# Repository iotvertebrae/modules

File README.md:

# IoT Vertebrae 

The vertebrae bus is an extenxion of the [UEXT](https://www.olimex.com/Products/Modules/UEXT) open bus proposed by Olimex.

This project will be provided as open-source hardware.

## [Using IoT Vertebrae (Wiki)](https://www-binefa-com.translate.goog/index.php/IoT-Vertebrae?_x_tr_sl=ca&_x_tr_tl=en&_x_tr_hl=es&_x_tr_pto=wapp)

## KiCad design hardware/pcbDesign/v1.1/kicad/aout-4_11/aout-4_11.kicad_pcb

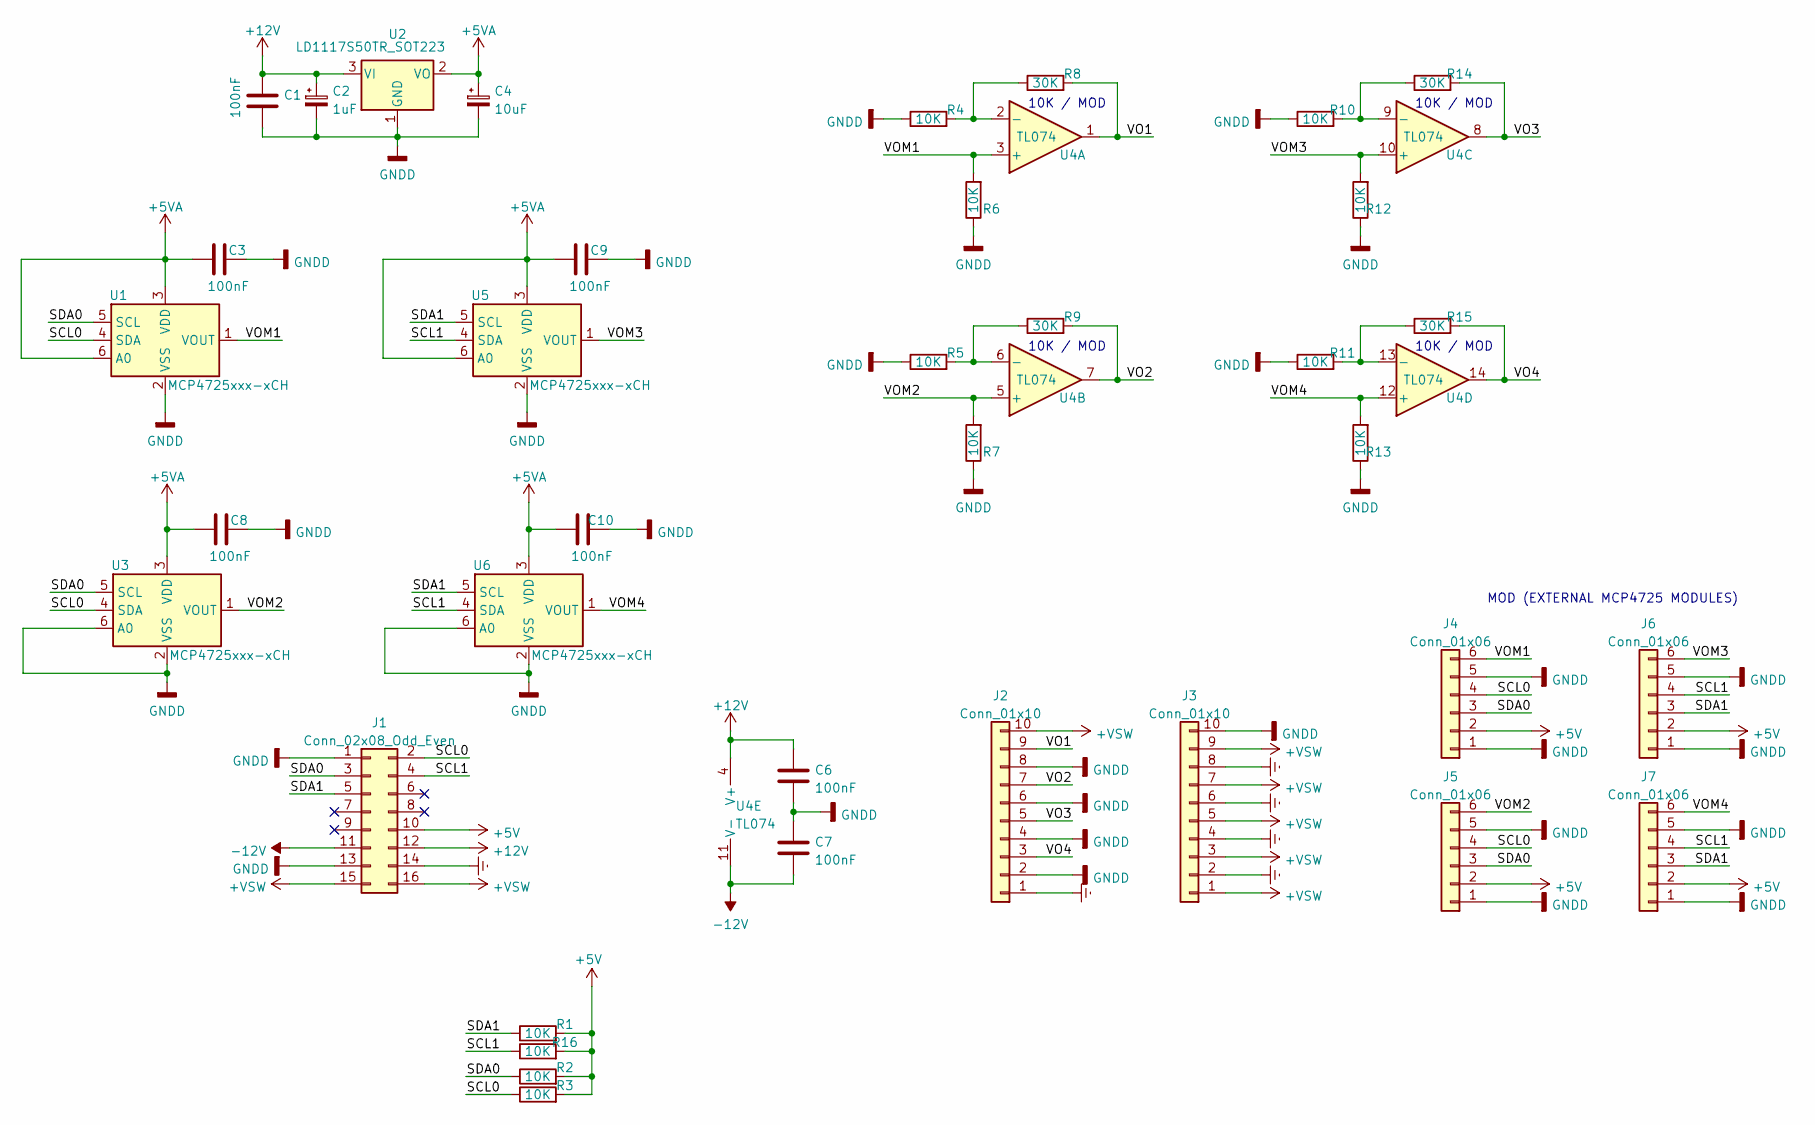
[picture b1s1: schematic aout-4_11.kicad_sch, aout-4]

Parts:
C1, C3, C6, C7, C8, C9, C10: 100nF; C_0805_2012Metric_Pad1.18x1.45mm_HandSolder
C2: 1uF; C_0805_2012Metric_Pad1.18x1.45mm_HandSolder
C4: 10uF; C_0805_2012Metric_Pad1.18x1.45mm_HandSolder
J1: Conn_02x08_Odd_Even; PinHeader_2x08_P2.54mm_Vertical
J2: Conn_01x10; PhoenixContact_MSTBA_2,5_10-G-5,08_1x10_P5.08mm_Horizontal
J3: Conn_01x10; PhoenixContact_MSTBVA_2,5_10-G-5,08_1x10_P5.08mm_Vertical
J4, J5, J6, J7: Conn_01x06; PinSocket_1x06_P2.54mm_Vertical
R1, R2, R3, R4, R5, R6, R7, R10, R11, R12, R13, R16: 10K; R_0805_2012Metric_Pad1.20x1.40mm_HandSolder
R8, R9, R14, R15: 30K; R_0805_2012Metric_Pad1.20x1.40mm_HandSolder
U1, U3, U5, U6: MCP4725xxx-xCH; SOT-23-6
U2: LD1117S50TR_SOT223; SOT-223-3_TabPin2
U4: TL074; SOIC-14_3.9x8.7mm_P1.27mm

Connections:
+5V: J1.10, J4.2, J5.2, J6.2, J7.2, R1.2, R2.2, R3.2, R16.2
+5VA: C3.1, C4.1, C8.1, C9.1, C10.1, U1.3 (VDD), U1.6 (A0), U2.2 (VO), U3.3 (VDD), U5.3 (VDD), U5.6 (A0), U6.3 (VDD)
+12V: C1.1, C2.1, C6.1, J1.12, U2.3 (VI), U4.4 (V+)
+VSW: J1.15, J1.16, J2.10, J3.1, J3.3, J3.5, J3.7, J3.9
-12V: C7.2, J1.11, U4.11 (V-)
/SCL0: J1.2, J4.4, J5.4, R3.1, U1.4 (SDA), U3.4 (SDA)
/SCL1: J1.4, J6.4, J7.4, R16.1, U5.4 (SDA), U6.4 (SDA)
/SDA0: J1.3, J4.3, J5.3, R2.1, U1.5 (SCL), U3.5 (SCL)
/SDA1: J1.5, J6.3, J7.3, R1.1, U5.5 (SCL), U6.5 (SCL)
/VO1: J2.9, R8.2, U4.1
/VO2: J2.7, R9.2, U4.7
/VO3: J2.5, R14.2, U4.8
/VO4: J2.3, R15.2, U4.14
/VOM1: J4.6, R6.2, U1.1 (VOUT), U4.3 (+)
/VOM2: J5.6, R7.2, U3.1 (VOUT), U4.5 (+)
/VOM3: J6.6, R12.2, U4.10 (+), U5.1 (VOUT)
/VOM4: J7.6, R13.2, U4.12 (+), U6.1 (VOUT)
Earth: J1.14, J2.1, J3.2, J3.4, J3.6, J3.8
GNDD: C1.2, C2.2, C3.2, C4.2, C6.2, C7.1, C8.2, C9.2, C10.2, J1.1, J1.13, J2.2, J2.4, J2.6, J2.8, J3.10, J4.1, J4.5, J5.1, J5.5, J6.1, J6.5, J7.1, J7.5, R4.1, R5.1, R6.1, R7.1, R10.1, R11.1, R12.1, R13.1, U1.2 (VSS), U2.1 (GND), U3.2 (VSS), U3.6 (A0), U5.2 (VSS), U6.2 (VSS), U6.6 (A0)
unnamed: R4.2, R8.1, U4.2 (-)
unnamed: R5.2, R9.1, U4.6 (-)
unnamed: R10.2, R14.1, U4.9 (-)
unnamed: R11.2, R15.1, U4.13 (-)

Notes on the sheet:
10K / MOD
MOD (EXTERNAL MCP4725 MODULES)

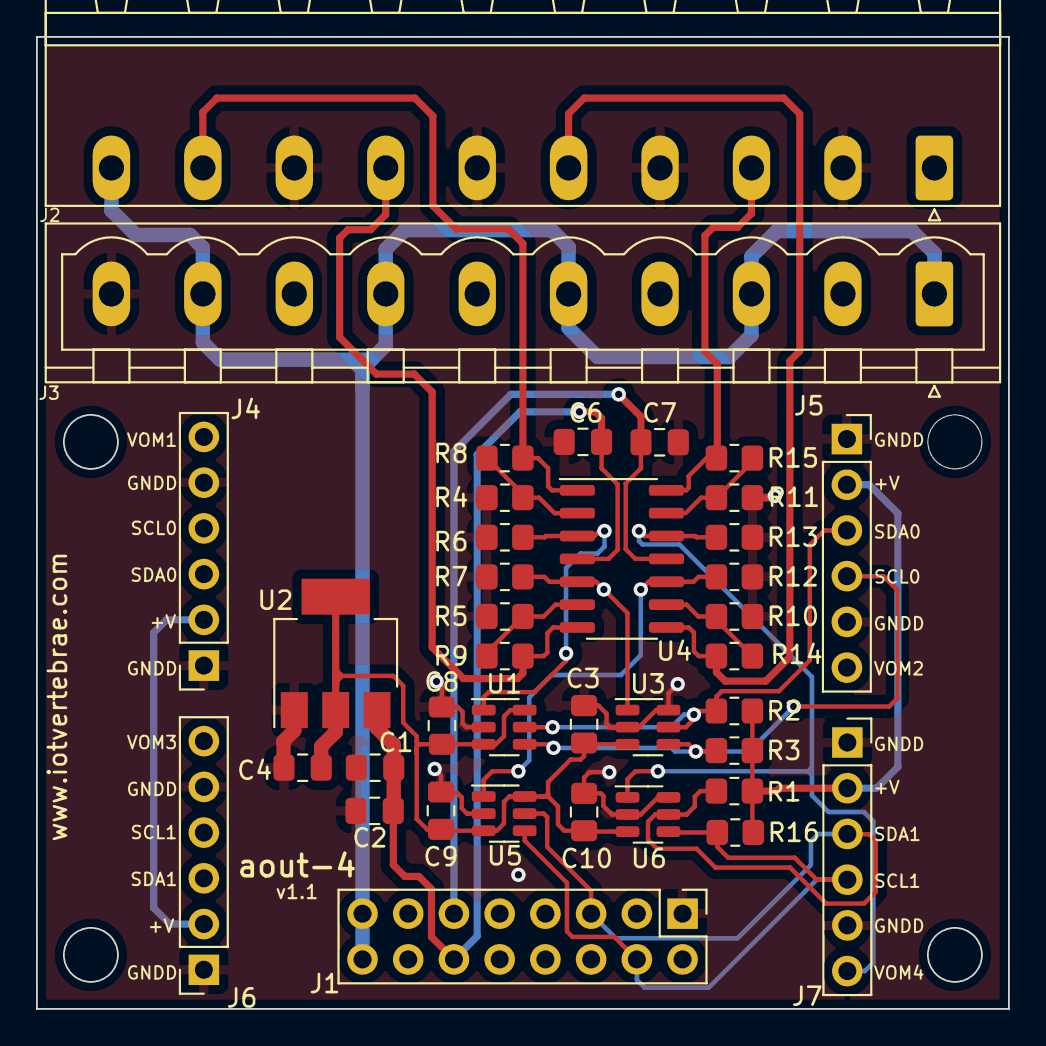
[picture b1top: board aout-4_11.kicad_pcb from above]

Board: 4 copper layers, 54.0 x 54.0 mm, 38 parts (0 on the bottom side), 23 nets.

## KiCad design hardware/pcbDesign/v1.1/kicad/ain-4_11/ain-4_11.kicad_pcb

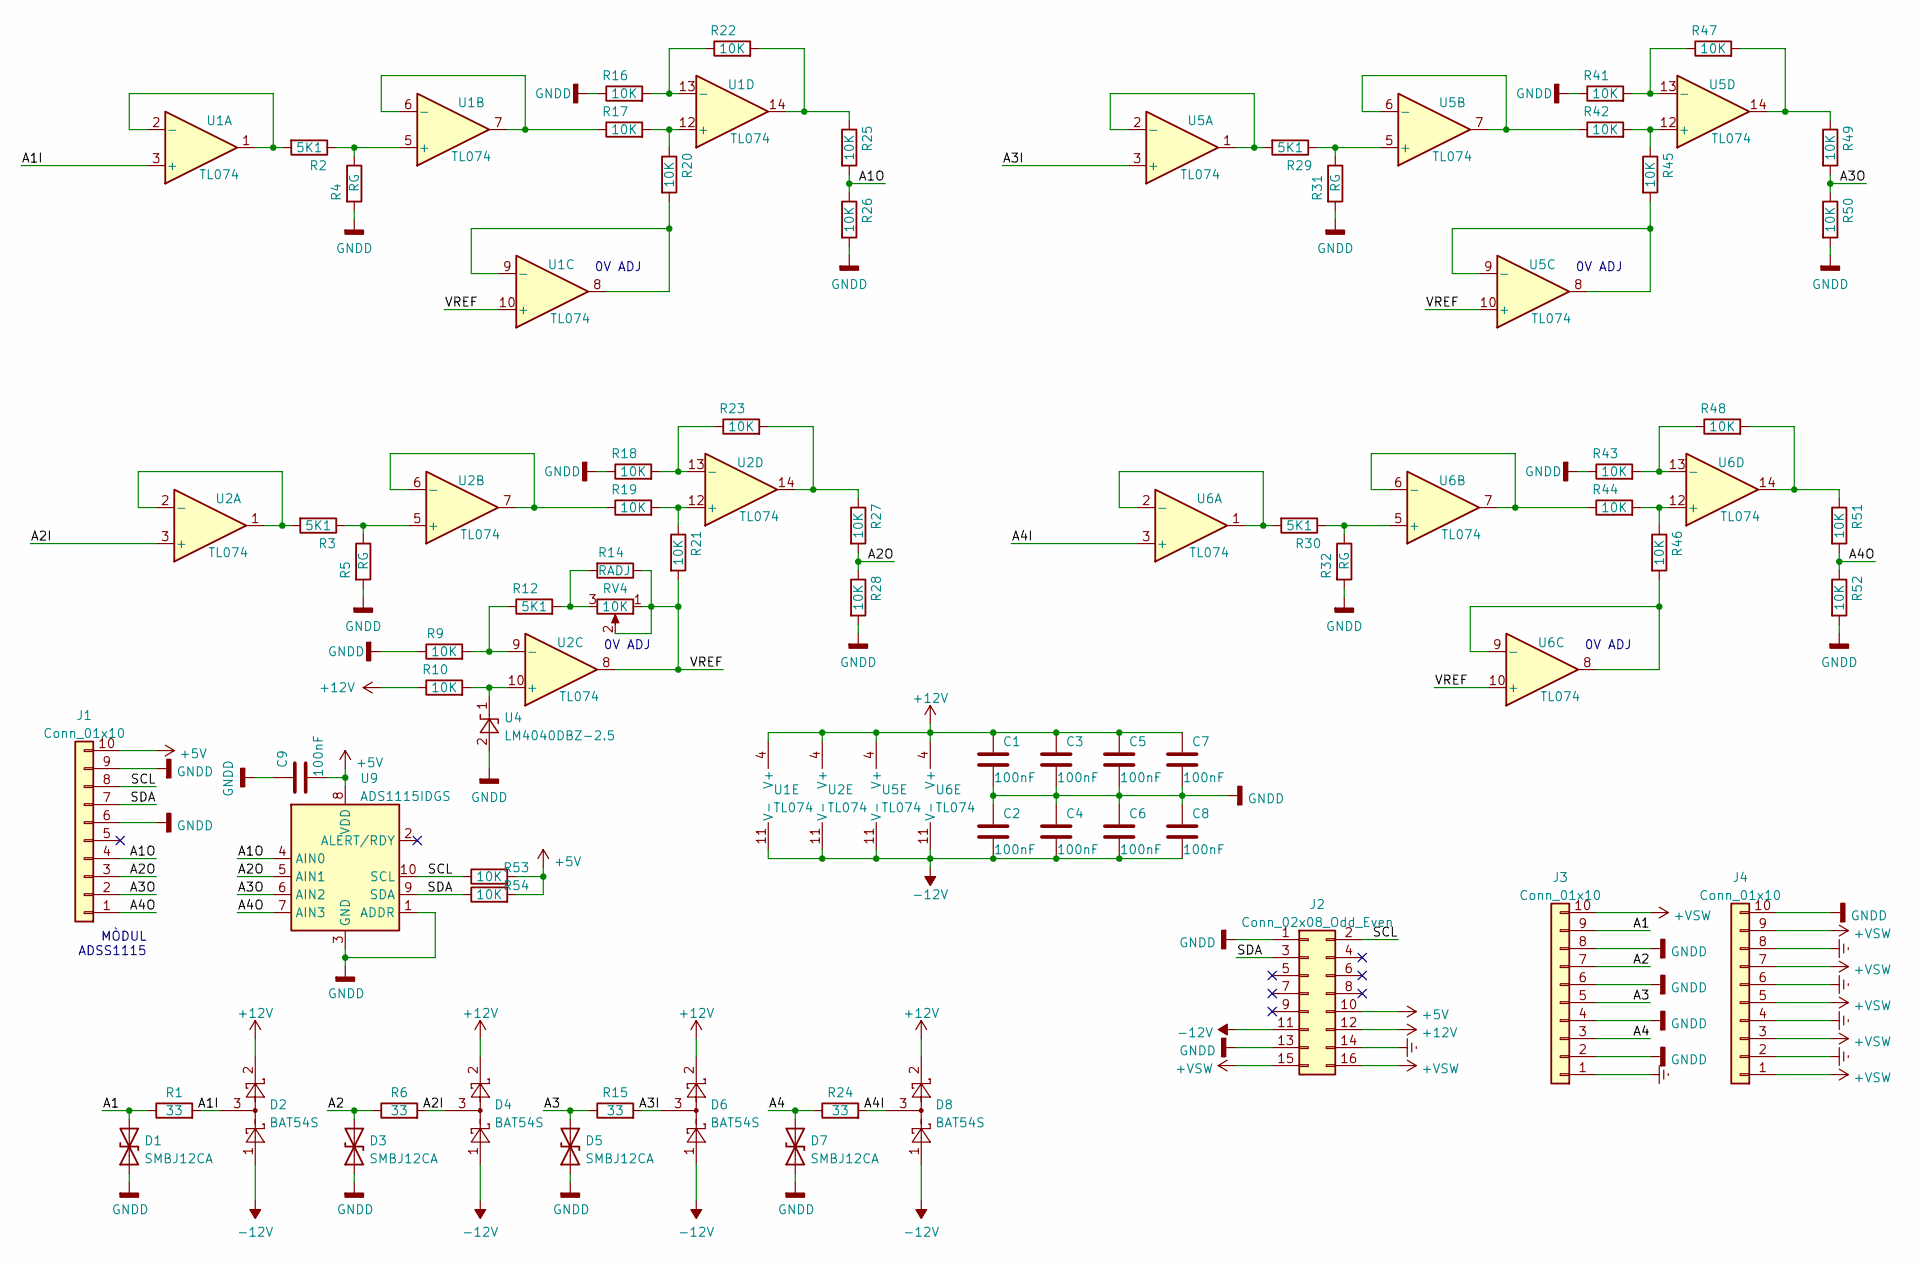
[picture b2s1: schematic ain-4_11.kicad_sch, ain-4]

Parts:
C1, C2, C3, C4, C5, C6, C7, C8, C9: 100nF; C_0805_2012Metric_Pad1.18x1.45mm_HandSolder
D1, D3, D5, D7: SMBJ12CA; D_SMB_Handsoldering
D2, D4, D6, D8: BAT54S; SOT-23
J1: Conn_01x10; PinSocket_1x10_P2.54mm_Vertical
J2: Conn_02x08_Odd_Even; PinHeader_2x08_P2.54mm_Vertical
J3: Conn_01x10; PhoenixContact_MSTBA_2,5_10-G_1x10_P5.00mm_Horizontal
J4: Conn_01x10; PhoenixContact_MSTBVA_2,5_10-G-5,08_1x10_P5.08mm_Vertical
R1, R6, R15, R24: 33; R_0805_2012Metric_Pad1.20x1.40mm_HandSolder
R2, R3, R12, R29, R30: 5K1; R_0805_2012Metric_Pad1.20x1.40mm_HandSolder
R4, R5, R31, R32: RG; R_0805_2012Metric_Pad1.20x1.40mm_HandSolder
R9, R10, R16, R17, R18, R19, R20, R21, R22, R23, R25, R26, R27, R28, R41, R42, R43, R44, R45, R46, R47, R48, R49, R50, R51, R52, R53, R54: 10K; R_0805_2012Metric_Pad1.20x1.40mm_HandSolder
R14: RADJ; R_0805_2012Metric_Pad1.20x1.40mm_HandSolder
RV4: 10K; Potentiometer_Bourns_3296W_Vertical
U1, U2, U5, U6: TL074; SOIC-14_3.9x8.7mm_P1.27mm
U4: LM4040DBZ-2.5; SOT-23
U9: ADS1115IDGS; TSSOP-10_3x3mm_P0.5mm

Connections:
+5V: C9.2, J1.10, J2.10, R53.2, R54.2, U9.8 (VDD)
+12V: C1.1, C3.1, C5.1, C7.1, D2.2, D4.2, D6.2, D8.2, J2.12, R10.1, U1.4 (V+), U2.4 (V+), U5.4 (V+), U6.4 (V+)
+VSW: J2.15, J2.16, J3.10, J4.1, J4.3, J4.5, J4.7, J4.9
-12V: C2.2, C4.2, C6.2, C8.2, D2.1, D4.1, D6.1, D8.1, J2.11, U1.11 (V-), U2.11 (V-), U5.11 (V-), U6.11 (V-)
/A1: D1.2 (A2), J3.9, R1.1
/A1I: D2.3, R1.2, U1.3 (+)
/A1O: J1.4, R25.2, R26.1, U9.4 (AIN0)
/A2: D3.2 (A2), J3.7, R6.1
/A2I: D4.3, R6.2, U2.3 (+)
/A2O: J1.3, R27.2, R28.1, U9.5 (AIN1)
/A3: D5.2 (A2), J3.5, R15.1
/A3I: D6.3, R15.2, U5.3 (+)
/A3O: J1.2, R49.2, R50.1, U9.6 (AIN2)
/A4: D7.2 (A2), J3.3, R24.1
/A4I: D8.3, R24.2, U6.3 (+)
/A4O: J1.1, R51.2, R52.1, U9.7 (AIN3)
/SCL: J1.8, J2.2, R53.1, U9.10 (SCL)
/SDA: J1.7, J2.3, R54.1, U9.9 (SDA)
/VREF: R14.1, R21.2, RV4.1, RV4.2, U1.10 (+), U2.8, U5.10 (+), U6.10 (+)
Earth: J2.14, J3.1, J4.2, J4.4, J4.6, J4.8
GNDD: C1.2, C2.1, C3.2, C4.1, C5.2, C6.1, C7.2, C8.1, C9.1, D1.1 (A1), D3.1 (A1), D5.1 (A1), D7.1 (A1), J1.6, J1.9, J2.1, J2.13, J3.2, J3.4, J3.6, J3.8, J4.10, R4.2, R5.2, R9.1, R16.1, R18.1, R26.2, R28.2, R31.2, R32.2, R41.1, R43.1, R50.2, R52.2, U4.2 (A), U9.1 (ADDR), U9.3 (GND)
unnamed: R2.1, R4.1, U1.5 (+)
unnamed: R2.2, U1.1, U1.2 (-)
unnamed: R3.1, R5.1, U2.5 (+)
unnamed: R3.2, U2.1, U2.2 (-)
unnamed: R10.2, U2.10 (+), U4.1 (K)
unnamed: R9.2, R12.1, U2.9 (-)
unnamed: R12.2, R14.2, RV4.3
unnamed: R16.2, R22.1, U1.13 (-)
unnamed: R17.1, U1.6 (-), U1.7
unnamed: R17.2, R20.1, U1.12 (+)
unnamed: R18.2, R23.1, U2.13 (-)
unnamed: R19.1, U2.6 (-), U2.7
unnamed: R19.2, R21.1, U2.12 (+)
unnamed: R20.2, U1.8, U1.9 (-)
unnamed: R22.2, R25.1, U1.14
unnamed: R23.2, R27.1, U2.14
unnamed: R29.1, R31.1, U5.5 (+)
unnamed: R29.2, U5.1, U5.2 (-)
unnamed: R30.1, R32.1, U6.5 (+)
unnamed: R30.2, U6.1, U6.2 (-)
unnamed: R41.2, R47.1, U5.13 (-)
unnamed: R42.1, U5.6 (-), U5.7
unnamed: R42.2, R45.1, U5.12 (+)
unnamed: R43.2, R48.1, U6.13 (-)
unnamed: R44.1, U6.6 (-), U6.7
unnamed: R44.2, R46.1, U6.12 (+)
unnamed: R45.2, U5.8, U5.9 (-)
unnamed: R46.2, U6.8, U6.9 (-)
unnamed: R47.2, R49.1, U5.14
unnamed: R48.2, R51.1, U6.14

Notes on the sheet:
0V ADJ
MÒDUL ADSS1115

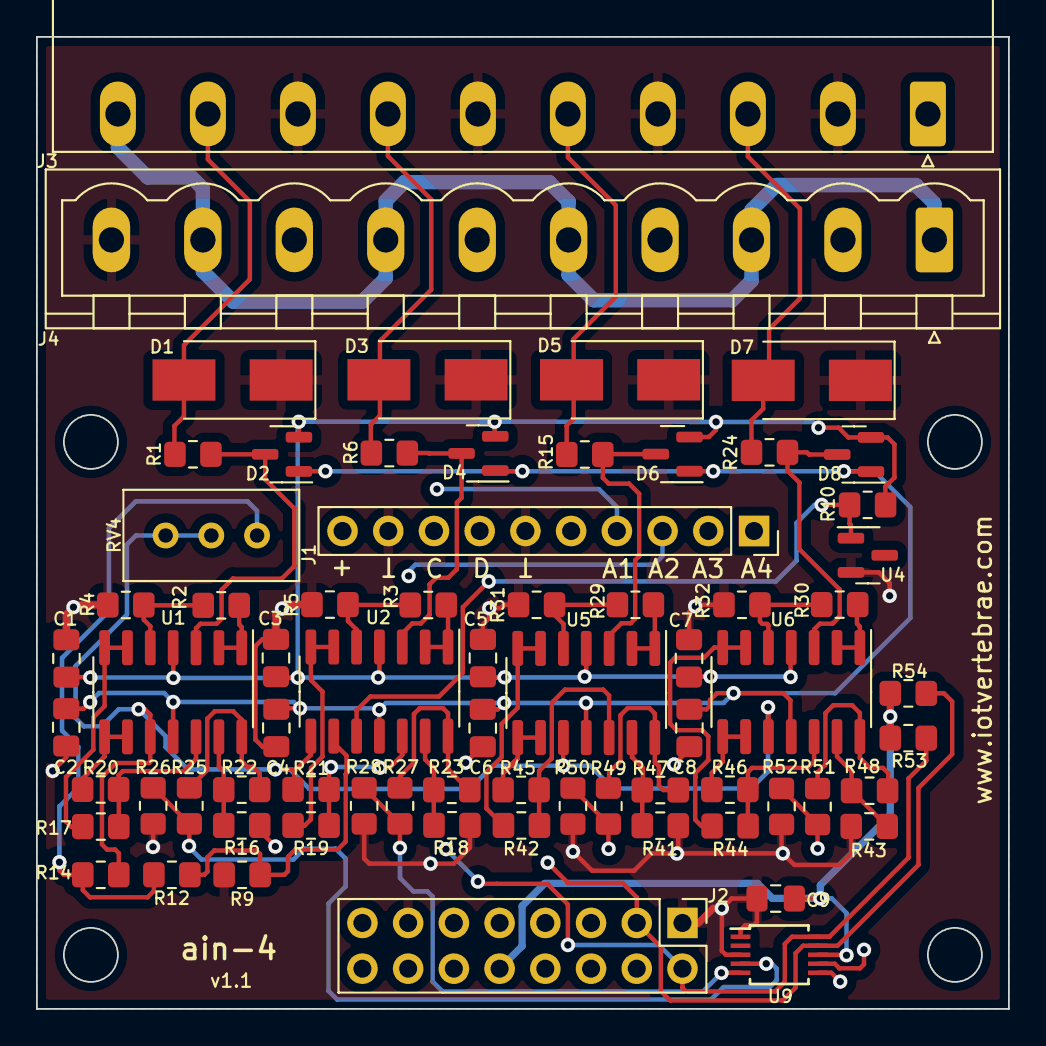
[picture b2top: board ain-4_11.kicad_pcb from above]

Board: 4 copper layers, 54.0 x 54.0 mm, 70 parts (0 on the bottom side), 51 nets.

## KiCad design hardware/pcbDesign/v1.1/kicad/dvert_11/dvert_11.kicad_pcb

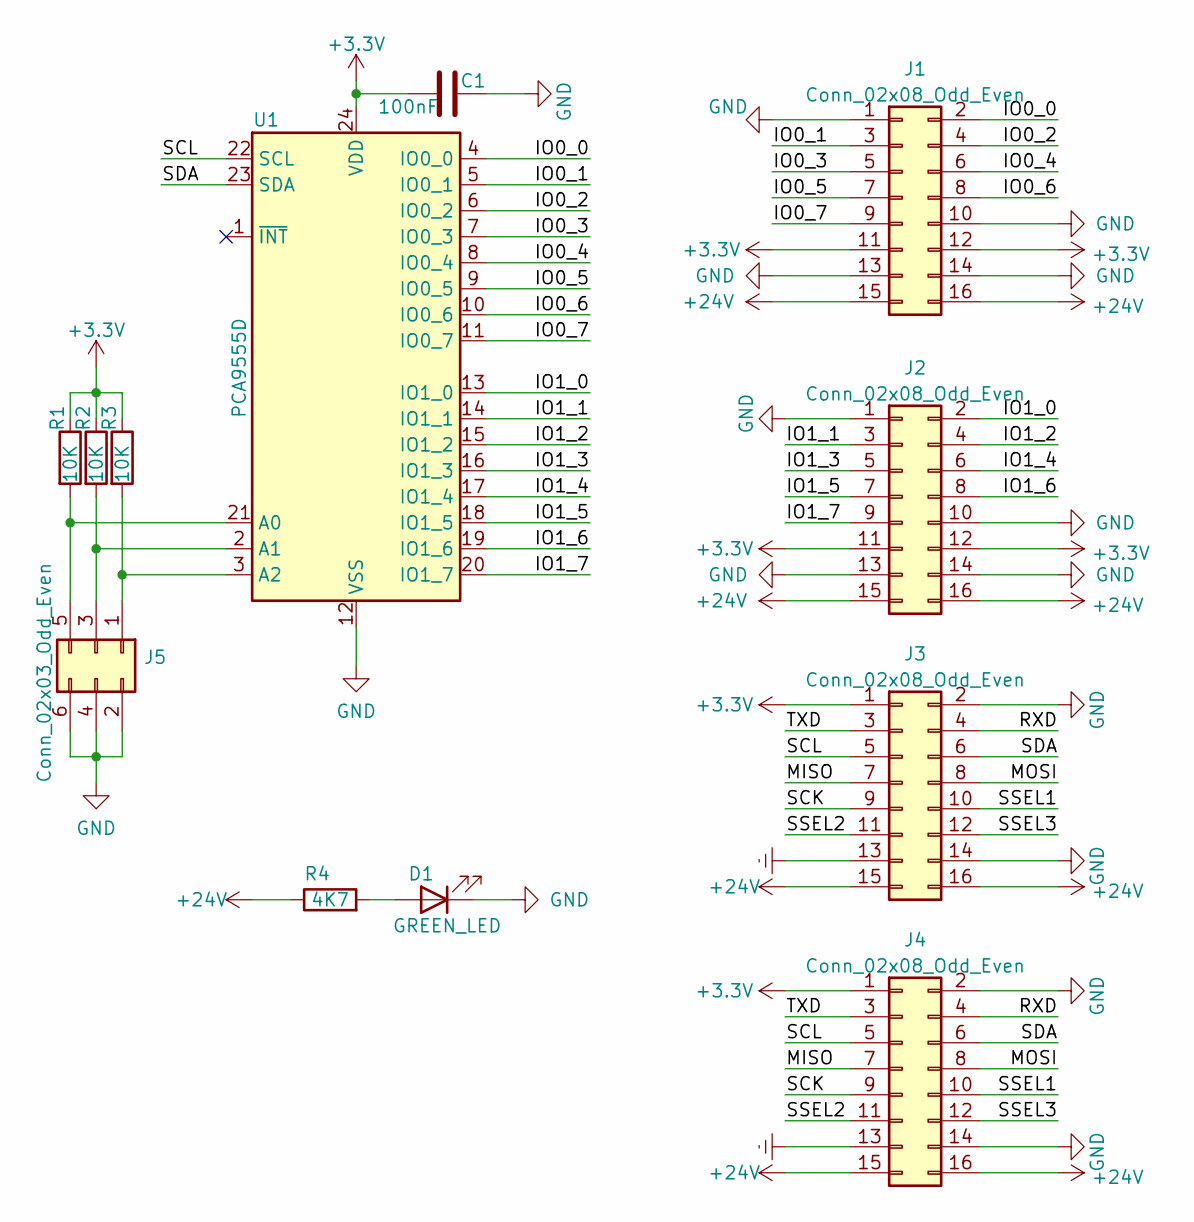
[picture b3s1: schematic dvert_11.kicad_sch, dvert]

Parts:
C1: 100nF; C_0805_2012Metric_Pad1.18x1.45mm_HandSolder
D1: GREEN_LED; LED_1206_3216Metric_Pad1.42x1.75mm_HandSolder
J1, J2, J3, J4: Conn_02x08_Odd_Even; PinHeader_2x08_P2.54mm_Vertical
J5: Conn_02x03_Odd_Even; PinHeader_2x03_P2.54mm_Vertical
R1, R2, R3: 10K; R_0805_2012Metric_Pad1.20x1.40mm_HandSolder
R4: 4K7; R_0805_2012Metric_Pad1.20x1.40mm_HandSolder
U1: PCA9555D; SOIC-24W_7.5x15.4mm_P1.27mm

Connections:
+3.3V: C1.1, J1.11, J1.12, J2.11, J2.12, J3.1, J4.1, R1.1, R2.1, R3.1, U1.24 (VDD)
+24V: J1.15, J1.16, J2.15, J2.16, J3.15, J3.16, J4.15, J4.16, R4.1
/IO0_0: J1.2, U1.4 (IO0_0)
/IO0_1: J1.3, U1.5 (IO0_1)
/IO0_2: J1.4, U1.6 (IO0_2)
/IO0_3: J1.5, U1.7 (IO0_3)
/IO0_4: J1.6, U1.8 (IO0_4)
/IO0_5: J1.7, U1.9 (IO0_5)
/IO0_6: J1.8, U1.10 (IO0_6)
/IO0_7: J1.9, U1.11 (IO0_7)
/IO1_0: J2.2, U1.13 (IO1_0)
/IO1_1: J2.3, U1.14 (IO1_1)
/IO1_2: J2.4, U1.15 (IO1_2)
/IO1_3: J2.5, U1.16 (IO1_3)
/IO1_4: J2.6, U1.17 (IO1_4)
/IO1_5: J2.7, U1.18 (IO1_5)
/IO1_6: J2.8, U1.19 (IO1_6)
/IO1_7: J2.9, U1.20 (IO1_7)
/MISO: J3.7, J4.7
/MOSI: J3.8, J4.8
/RXD: J3.4, J4.4
/SCK: J3.9, J4.9
/SCL: J3.5, J4.5, U1.22 (SCL)
/SDA: J3.6, J4.6, U1.23 (SDA)
/SSEL1: J3.10, J4.10
/SSEL2: J3.11, J4.11
/SSEL3: J3.12, J4.12
/TXD: J3.3, J4.3
Earth: J3.13, J4.13
GND: C1.2, D1.1 (K), J1.1, J1.10, J1.13, J1.14, J2.1, J2.10, J2.13, J2.14, J3.2, J3.14, J4.2, J4.14, J5.2, J5.4, J5.6, U1.12 (VSS)
unnamed: D1.2 (A), R4.2
unnamed: J5.1, R3.2, U1.3 (A2)
unnamed: J5.3, R2.2, U1.2 (A1)
unnamed: J5.5, R1.2, U1.21 (A0)

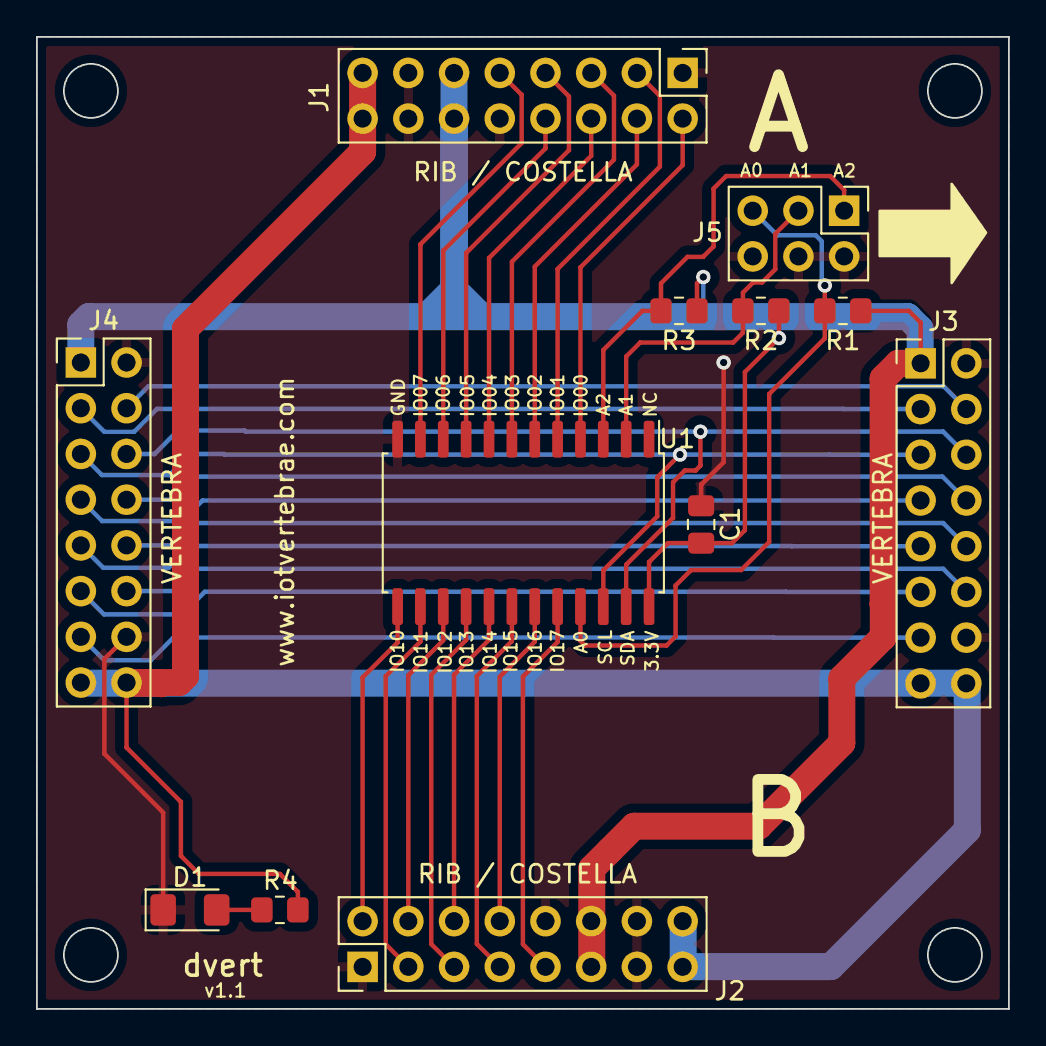
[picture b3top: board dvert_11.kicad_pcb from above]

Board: 2 copper layers, 54.0 x 54.0 mm, 12 parts (0 on the bottom side), 34 nets.

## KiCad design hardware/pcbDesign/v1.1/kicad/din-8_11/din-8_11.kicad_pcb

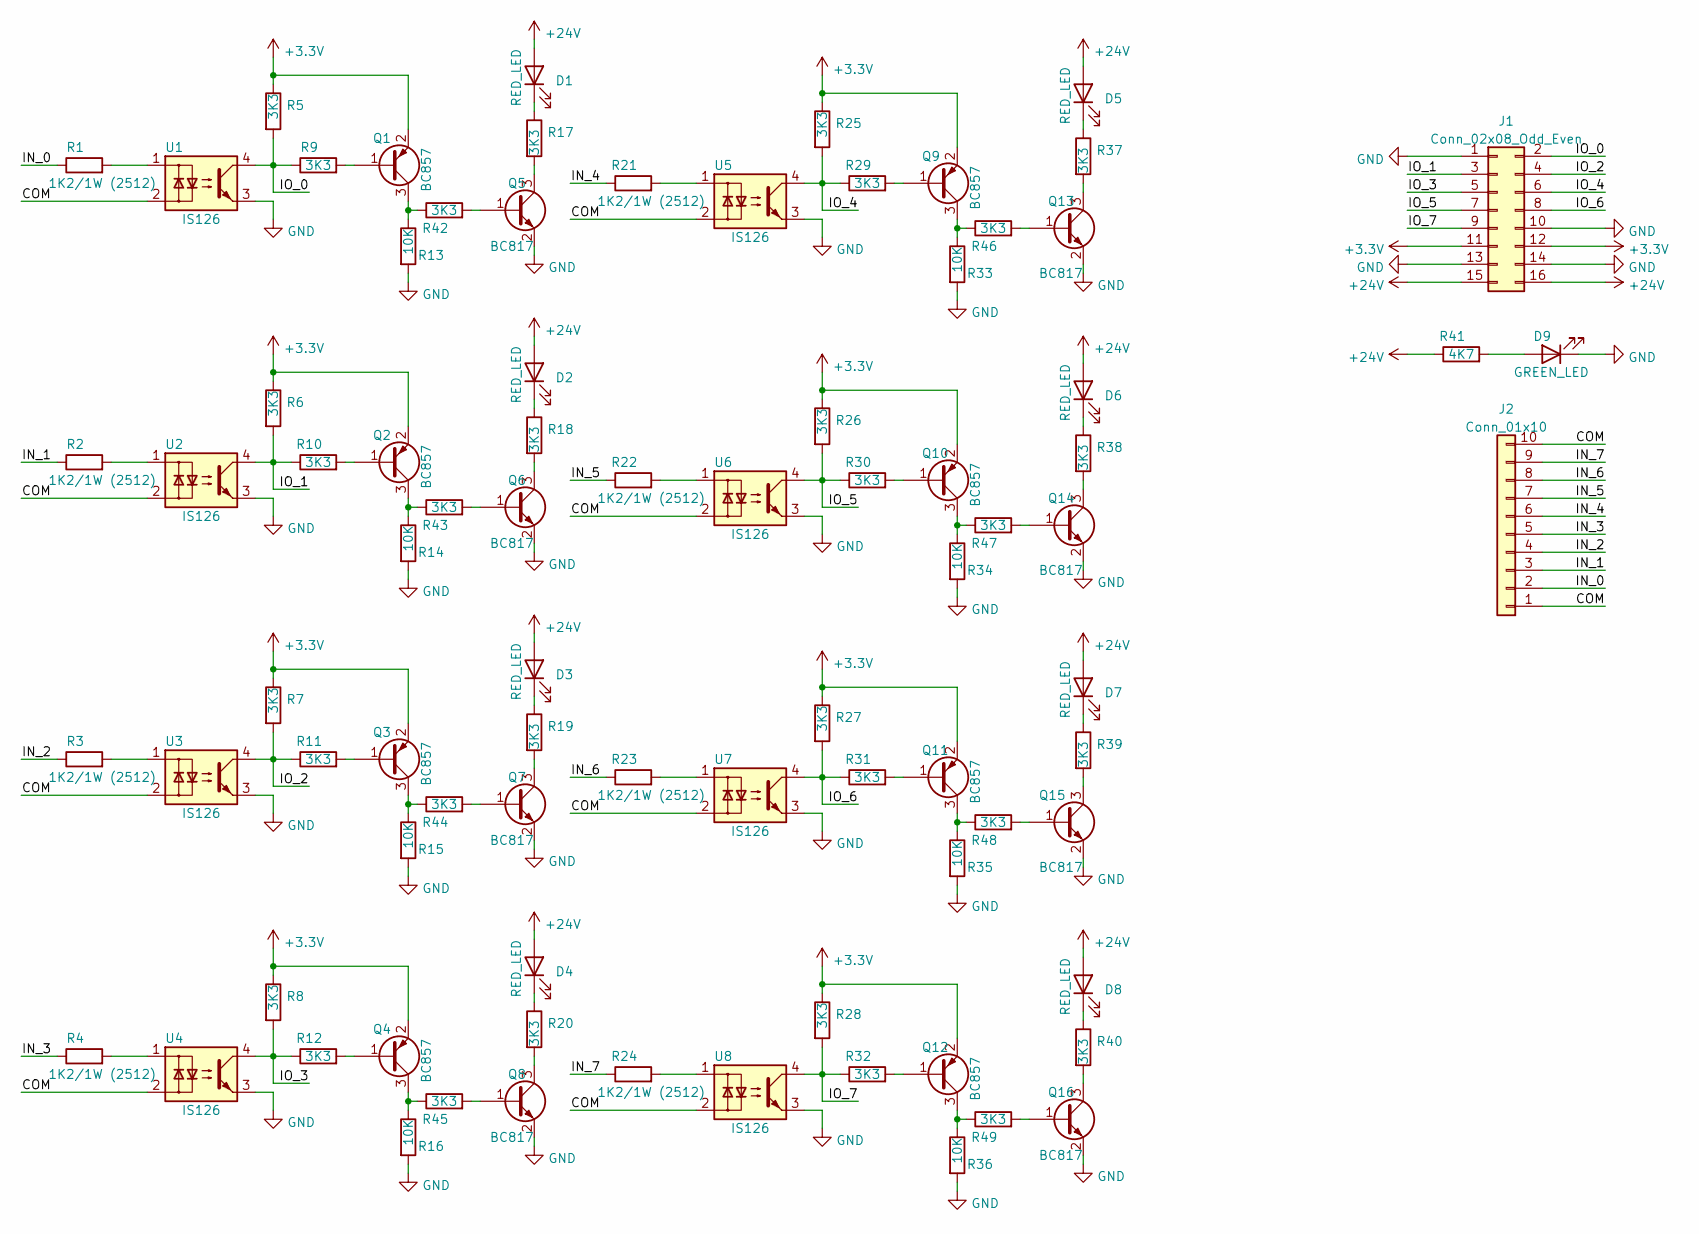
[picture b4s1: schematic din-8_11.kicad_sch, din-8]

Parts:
D1, D2, D3, D4, D5, D6, D7, D8: RED_LED; LED_1206_3216Metric_Pad1.42x1.75mm_HandSolder
D9: GREEN_LED; LED_1206_3216Metric_Pad1.42x1.75mm_HandSolder
J1: Conn_02x08_Odd_Even; PinHeader_2x08_P2.54mm_Vertical
J2: Conn_01x10; PhoenixContact_MSTBA_2,5_10-G-5,08_1x10_P5.08mm_Horizontal
Q1, Q2, Q3, Q4, Q9, Q10, Q11, Q12: BC857; SOT-23
Q5, Q6, Q7, Q8, Q13, Q14, Q15, Q16: BC817; SOT-23
R1, R2, R3, R4, R21, R22, R23, R24: 1K2/1W (2512); R_2512_6332Metric_Pad1.40x3.35mm_HandSolder
R5, R6, R7, R8, R9, R10, R11, R12, R17, R18, R19, R20, R25, R26, R27, R28, R29, R30, R31, R32, R37, R38, R39, R40, R42, R43, R44, R45, R46, R47, R48, R49: 3K3; R_0805_2012Metric_Pad1.20x1.40mm_HandSolder
R13, R14, R15, R16, R33, R34, R35, R36: 10K; R_0805_2012Metric_Pad1.20x1.40mm_HandSolder
R41: 4K7; R_0805_2012Metric_Pad1.20x1.40mm_HandSolder
U1, U2, U3, U4, U5, U6, U7, U8: IS126; SOIC-4_IS126_4.55x3.7mm_P2.54mm

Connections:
+3.3V: J1.11, J1.12, Q1.2 (E), Q2.2 (E), Q3.2 (E), Q4.2 (E), Q9.2 (E), Q10.2 (E), Q11.2 (E), Q12.2 (E), R5.1, R6.1, R7.1, R8.1, R25.1, R26.1, R27.1, R28.1
+24V: D1.2 (A), D2.2 (A), D3.2 (A), D4.2 (A), D5.2 (A), D6.2 (A), D7.2 (A), D8.2 (A), J1.15, J1.16, R41.1
/COM: J2.1, J2.10, U1.2, U2.2, U3.2, U4.2, U5.2, U6.2, U7.2, U8.2
/IN_0: J2.2, R1.1
/IN_1: J2.3, R2.1
/IN_2: J2.4, R3.1
/IN_3: J2.5, R4.1
/IN_4: J2.6, R21.1
/IN_5: J2.7, R22.1
/IN_6: J2.8, R23.1
/IN_7: J2.9, R24.1
/IO_0: J1.2, R5.2, R9.1, U1.4
/IO_1: J1.3, R6.2, R10.1, U2.4
/IO_2: J1.4, R7.2, R11.1, U3.4
/IO_3: J1.5, R8.2, R12.1, U4.4
/IO_4: J1.6, R25.2, R29.1, U5.4
/IO_5: J1.7, R26.2, R30.1, U6.4
/IO_6: J1.8, R27.2, R31.1, U7.4
/IO_7: J1.9, R28.2, R32.1, U8.4
GND: D9.1 (K), J1.1, J1.10, J1.13, J1.14, Q5.2 (E), Q6.2 (E), Q7.2 (E), Q8.2 (E), Q13.2 (E), Q14.2 (E), Q15.2 (E), Q16.2 (E), R13.2, R14.2, R15.2, R16.2, R33.2, R34.2, R35.2, R36.2, U1.3, U2.3, U3.3, U4.3, U5.3, U6.3, U7.3, U8.3
unnamed: D1.1 (K), R17.1
unnamed: D2.1 (K), R18.1
unnamed: D3.1 (K), R19.1
unnamed: D4.1 (K), R20.1
unnamed: D5.1 (K), R37.1
unnamed: D6.1 (K), R38.1
unnamed: D7.1 (K), R39.1
unnamed: D8.1 (K), R40.1
unnamed: D9.2 (A), R41.2
unnamed: Q1.1 (B), R9.2
unnamed: Q1.3 (C), R13.1, R42.1
unnamed: Q2.1 (B), R10.2
unnamed: Q2.3 (C), R14.1, R43.1
unnamed: Q3.1 (B), R11.2
unnamed: Q3.3 (C), R15.1, R44.1
unnamed: Q4.1 (B), R12.2
unnamed: Q4.3 (C), R16.1, R45.1
unnamed: Q5.1 (B), R42.2
unnamed: Q5.3 (C), R17.2
unnamed: Q6.1 (B), R43.2
unnamed: Q6.3 (C), R18.2
unnamed: Q7.1 (B), R44.2
unnamed: Q7.3 (C), R19.2
unnamed: Q8.1 (B), R45.2
unnamed: Q8.3 (C), R20.2
unnamed: Q9.1 (B), R29.2
unnamed: Q9.3 (C), R33.1, R46.1
unnamed: Q10.1 (B), R30.2
unnamed: Q10.3 (C), R34.1, R47.1
unnamed: Q11.1 (B), R31.2
unnamed: Q11.3 (C), R35.1, R48.1
unnamed: Q12.1 (B), R32.2
unnamed: Q12.3 (C), R36.1, R49.1
unnamed: Q13.1 (B), R46.2
unnamed: Q13.3 (C), R37.2
unnamed: Q14.1 (B), R47.2
unnamed: Q14.3 (C), R38.2
unnamed: Q15.1 (B), R48.2
unnamed: Q15.3 (C), R39.2
unnamed: Q16.1 (B), R49.2
unnamed: Q16.3 (C), R40.2
unnamed: R1.2, U1.1
unnamed: R2.2, U2.1
unnamed: R3.2, U3.1
unnamed: R4.2, U4.1
unnamed: R21.2, U5.1
unnamed: R22.2, U6.1
unnamed: R23.2, U7.1
unnamed: R24.2, U8.1

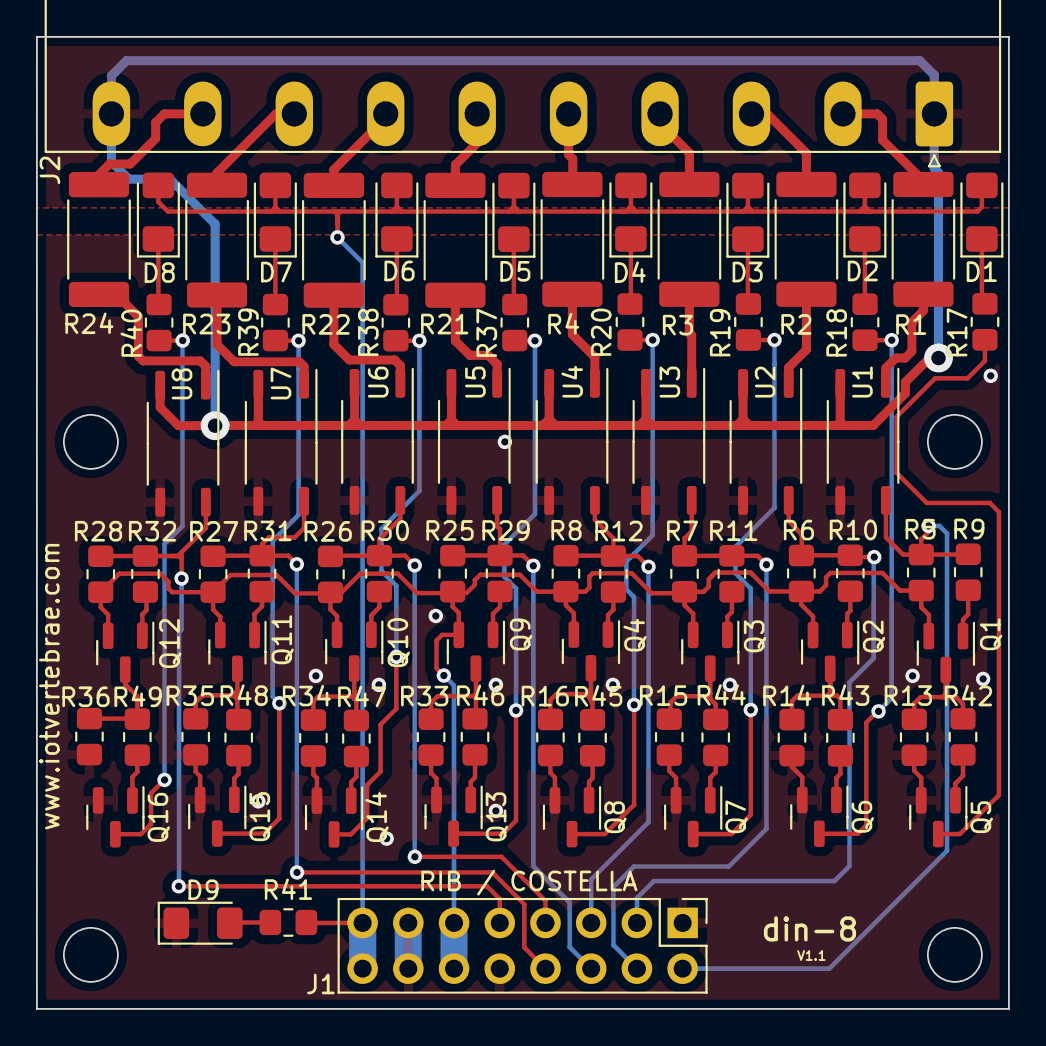
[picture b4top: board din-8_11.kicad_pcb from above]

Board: 2 copper layers, 54.0 x 54.0 mm, 84 parts (0 on the bottom side), 69 nets.

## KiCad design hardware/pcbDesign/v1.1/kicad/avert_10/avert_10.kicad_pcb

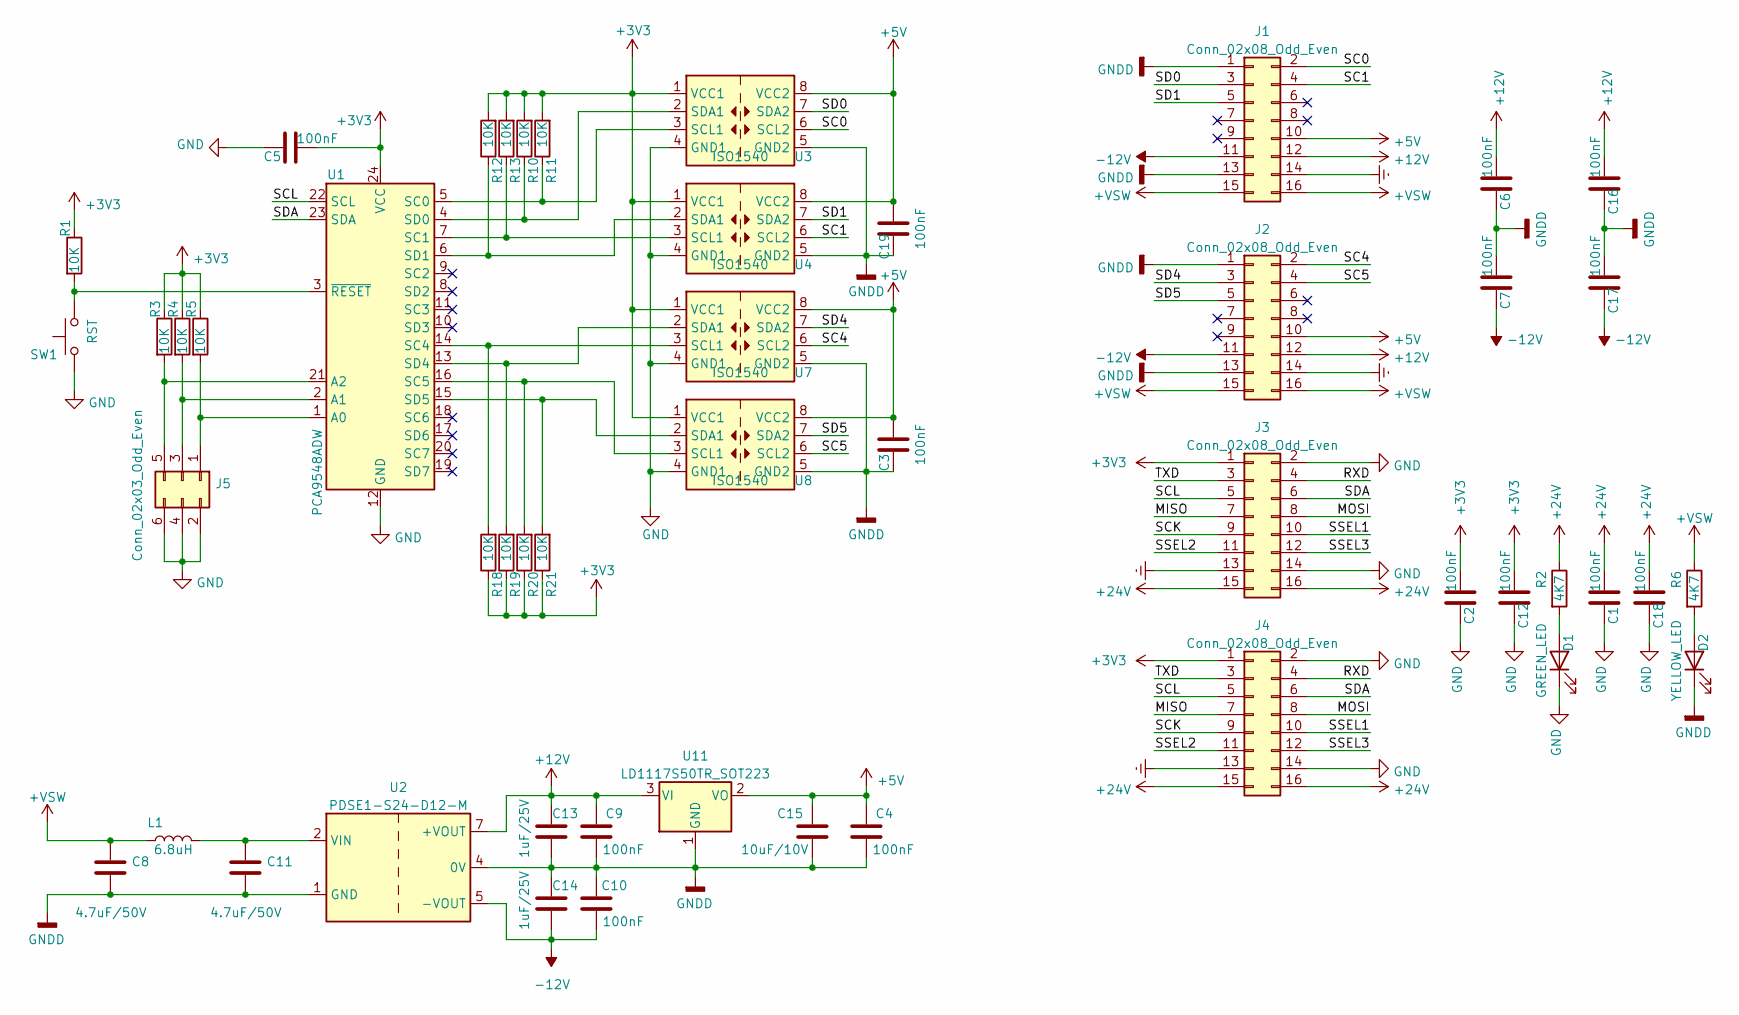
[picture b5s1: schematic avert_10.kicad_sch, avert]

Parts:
C1, C2, C3, C4, C5, C6, C7, C9, C10, C12, C16, C17, C18, C19: 100nF; C_0805_2012Metric_Pad1.18x1.45mm_HandSolder
C8, C11: 4.7uF/50V; C_0805_2012Metric_Pad1.18x1.45mm_HandSolder
C13, C14: 1uF/25V; C_0805_2012Metric_Pad1.18x1.45mm_HandSolder
C15: 10uF/10V; C_0805_2012Metric_Pad1.18x1.45mm_HandSolder
D1: GREEN_LED; LED_1206_3216Metric_Pad1.42x1.75mm_HandSolder
D2: YELLOW_LED; LED_1206_3216Metric_Pad1.42x1.75mm_HandSolder
J1, J2, J3, J4: Conn_02x08_Odd_Even; PinHeader_2x08_P2.54mm_Vertical
J5: Conn_02x03_Odd_Even; PinHeader_2x03_P2.54mm_Vertical
L1: 6.8uH; L_Bourns_SRP7028A_7.3x6.6mm
R1, R3, R4, R5, R10, R11, R12, R13, R18, R19, R20, R21: 10K; R_0805_2012Metric_Pad1.20x1.40mm_HandSolder
R2, R6: 4K7; R_0805_2012Metric_Pad1.20x1.40mm_HandSolder
SW1: RST; SW_SPST_CK_RS282G05A3
U1: PCA9548ADW; SOIC-24W_7.5x15.4mm_P1.27mm
U2: PDSE1-S24-D12-M; PDESE1-S24-D12-M
U3, U4, U7, U8: ISO1540; SOIC-8_3.9x4.9mm_P1.27mm
U11: LD1117S50TR_SOT223; SOT-223-3_TabPin2

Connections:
+3V3: C2.1, C5.1, C12.1, J3.1, J4.1, R1.1, R3.1, R4.1, R5.1, R10.2, R11.2, R12.2, R13.2, R18.1, R19.1, R20.1, R21.1, U1.24 (VCC), U3.1 (VCC1), U4.1 (VCC1), U7.1 (VCC1), U8.1 (VCC1)
+5V: C3.1, C4.1, C15.1, C19.1, J1.10, J2.10, U3.8 (VCC2), U4.8 (VCC2), U7.8 (VCC2), U8.8 (VCC2), U11.2 (VO)
+12V: C6.1, C9.1, C13.1, C16.1, J1.12, J2.12, U2.7 (+VOUT), U11.3 (VI)
+24V: C1.1, C18.1, J3.15, J3.16, J4.15, J4.16, R2.1
+VSW: C8.1, J1.15, J1.16, J2.15, J2.16, L1.1, R6.1
-12V: C7.2, C10.2, C14.2, C17.2, J1.11, J2.11, U2.5 (-VOUT)
/MISO: J3.7, J4.7
/MOSI: J3.8, J4.8
/RXD: J3.4, J4.4
/SC0: J1.2, U3.6 (SCL2)
/SC1: J1.4, U4.6 (SCL2)
/SC4: J2.2, U7.6 (SCL2)
/SC5: J2.4, U8.6 (SCL2)
/SCK: J3.9, J4.9
/SCL: J3.5, J4.5, U1.22 (SCL)
/SD0: J1.3, U3.7 (SDA2)
/SD1: J1.5, U4.7 (SDA2)
/SD4: J2.3, U7.7 (SDA2)
/SD5: J2.5, U8.7 (SDA2)
/SDA: J3.6, J4.6, U1.23 (SDA)
/SSEL1: J3.10, J4.10
/SSEL2: J3.11, J4.11
/SSEL3: J3.12, J4.12
/TXD: J3.3, J4.3
Earth: J1.14, J2.14, J3.13, J4.13
GND: C1.2, C2.2, C5.2, C12.2, C18.2, D1.1 (K), J3.2, J3.14, J4.2, J4.14, J5.2, J5.4, J5.6, SW1.1, U1.12 (GND), U3.4 (GND1), U4.4 (GND1), U7.4 (GND1), U8.4 (GND1)
GNDD: C3.2, C4.2, C6.2, C7.1, C8.2, C9.2, C10.1, C11.2, C13.2, C14.1, C15.2, C16.2, C17.1, C19.2, D2.1 (K), J1.1, J1.13, J2.1, J2.13, U2.1 (GND), U2.4 (0V), U3.5 (GND2), U4.5 (GND2), U7.5 (GND2), U8.5 (GND2), U11.1 (GND)
unnamed: C11.1, L1.2, U2.2 (VIN)
unnamed: D1.2 (A), R2.2
unnamed: D2.2 (A), R6.2
unnamed: J5.1, R5.2, U1.1 (A0)
unnamed: J5.3, R4.2, U1.2 (A1)
unnamed: J5.5, R3.2, U1.21 (A2)
unnamed: R1.2, SW1.2, U1.3 (~RESET)
unnamed: R10.1, U1.4 (SD0), U3.2 (SDA1)
unnamed: R11.1, U1.5 (SC0), U3.3 (SCL1)
unnamed: R12.1, U1.6 (SD1), U4.2 (SDA1)
unnamed: R13.1, U1.7 (SC1), U4.3 (SCL1)
unnamed: R18.2, U1.14 (SC4), U7.3 (SCL1)
unnamed: R19.2, U1.13 (SD4), U7.2 (SDA1)
unnamed: R20.2, U1.16 (SC5), U8.3 (SCL1)
unnamed: R21.2, U1.15 (SD5), U8.2 (SDA1)
